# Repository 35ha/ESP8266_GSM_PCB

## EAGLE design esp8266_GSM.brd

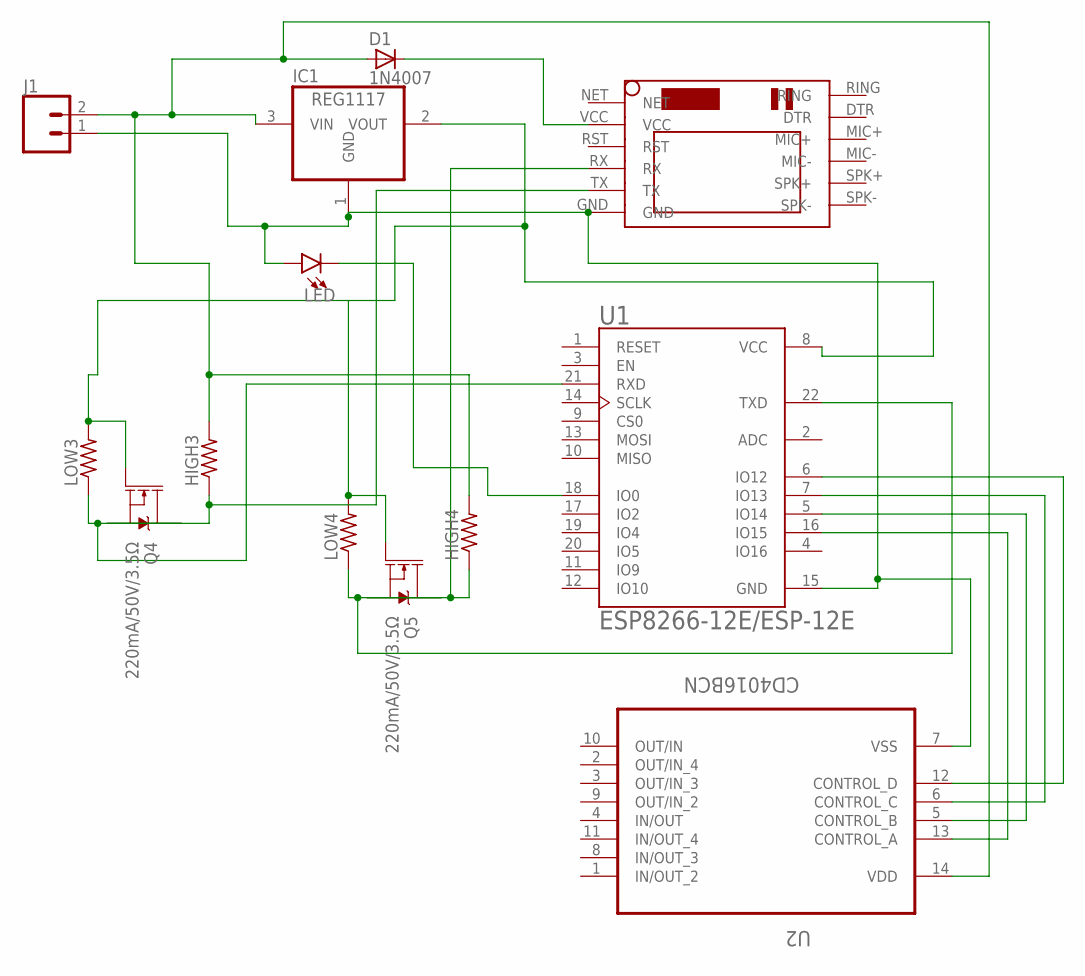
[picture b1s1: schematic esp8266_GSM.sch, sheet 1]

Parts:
D1: 1N4007; SMA
HIGH3, HIGH4: R-US_R1206; R1206
IC1: REG1117; SOT223
J1: CONN_025MM; SCREWTERMINAL-5MM-2
LED: LED1206; LED-1206
LOW3, LOW4: R-US_R1206; R1206
Q4, Q5: 220mA/50V/3.5Ω; SOT23-3
U1: ESP8266-12E/ESP-12E; XCVR_ESP8266-12E/ESP-12E
U2: CD4016BCN; DIP254P762X508-14
U$1: SIM800LMODULE

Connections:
unnamed: LED.C, U1.18 (IO0)
unnamed: D1.K (C), U$1.VCC
unnamed: IC1.1 (GND), J1.1, LED.A, U1.15 (GND), U2.7 (VSS), U$1.GND
unnamed: U1.6 (IO12), U2.12 (CONTROL_D)
unnamed: U1.7 (IO13), U2.6 (CONTROL_C)
unnamed: LOW3.1, Q4.3 (D), U1.21 (RXD)
unnamed: HIGH3.1, Q4.2 (S), U$1.TX
unnamed: U1.5 (IO14), U2.5 (CONTROL_B)
unnamed: LOW4.1, Q5.3 (D), U1.22 (TXD)
unnamed: HIGH4.1, Q5.2 (S), U$1.RX
unnamed: IC1.2 (VOUT), LOW3.2, LOW4.2, Q4.1 (G), Q5.1 (G), U1.8 (VCC)
unnamed: U1.16 (IO15), U2.13 (CONTROL_A)
unnamed: D1.A, HIGH3.2, HIGH4.2, IC1.3 (VIN), J1.2, U2.14 (VDD)

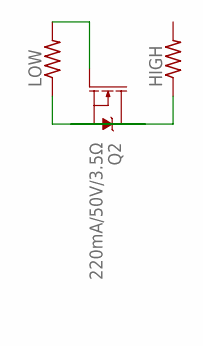
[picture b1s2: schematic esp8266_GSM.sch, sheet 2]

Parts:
HIGH: R-US_R1206; R1206
LOW: R-US_R1206; R1206
Q2: 220mA/50V/3.5Ω; SOT23-3

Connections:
unnamed: LOW.1, Q2.3 (D)
unnamed: HIGH.1, Q2.2 (S)
unnamed: LOW.2, Q2.1 (G)

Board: 2 copper layers, 16 parts (0 on the bottom side), 16 nets, no tracks yet.

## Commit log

2020-12-27 new file added
2020-12-27 components added

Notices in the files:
parts and their libraries:
SparkFun-Retired: Licensing: Creative Commons ShareAlike 4.0 International - https://creativecommons.org/licenses/by-sa/4.0
